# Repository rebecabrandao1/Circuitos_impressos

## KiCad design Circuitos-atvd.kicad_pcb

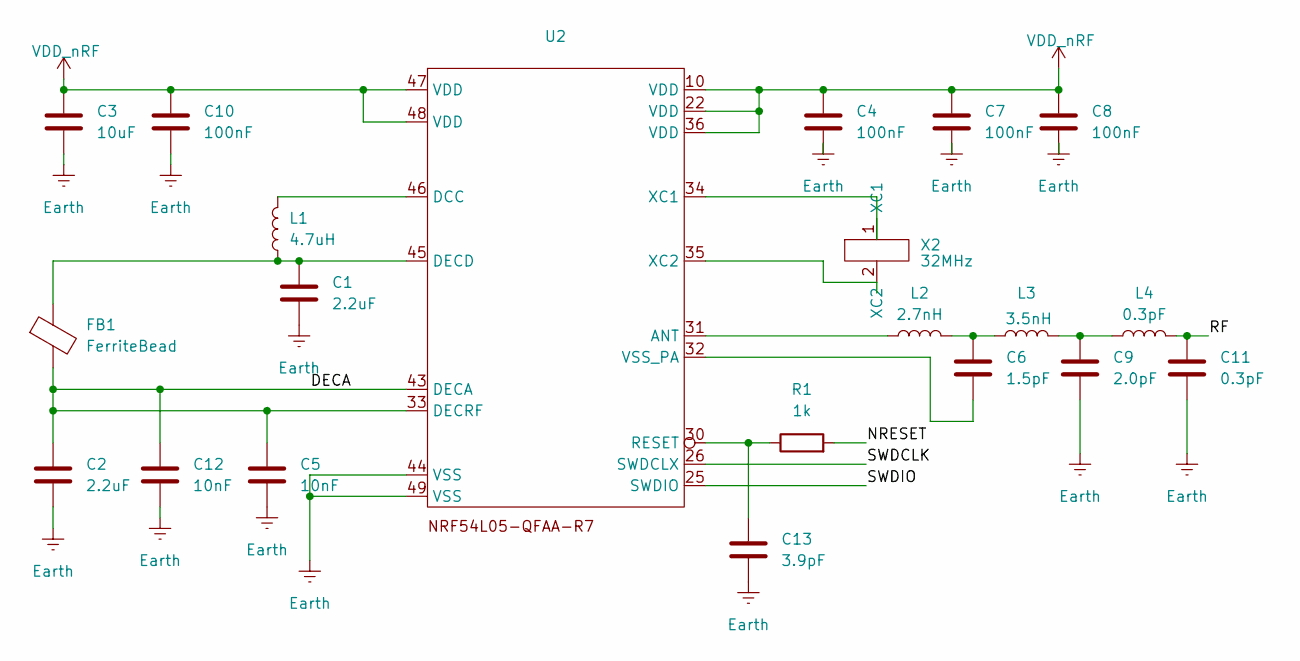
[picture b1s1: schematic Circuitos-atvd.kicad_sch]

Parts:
C1, C2: 2.2uF; C_0201_0603Metric
C3: 10uF; C_0402_1005Metric
C4, C7, C8, C10: 100nF; C_0201_0603Metric
C5, C12: 10nF; C_0201_0603Metric
C6: 1.5pF; C_0201_0603Metric
C9: 2.0pF; C_0201_0603Metric
C11: 0.3pF; C_0201_0603Metric
C13: 3.9pF; C_0201_0603Metric
FB1: FerriteBead; LairdTech_28C0236-0JW-10
L1: 4.7uH; L_0603_1608Metric
L2: 2.7nH; L_0201_0603Metric
L3: 3.5nH; L_0201_0603Metric
L4: 0.3pF; L_0201_0603Metric
R1: 1k; R_0201_0603Metric
U2: QFN-28-1EP_6x6mm_P0.65mm_EP4.25x4.25mm_ThermalVias
X2: 32MHz; Crystal_SMD_ECS_CSM3X-2Pin_7.6x4.1mm

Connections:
/DECA: C2.1, C5.1, C12.1, FB1.2, U2.33 (DECRF), U2.43 (DECA); also elsewhere on the board
/NRESET: R1.2
/RF: C11.1, L4.2
GND: C1.2, C2.2, C3.2, C4.2, C5.2, C7.2, C8.2, C9.2, C10.2, C11.2, C12.2, C13.2, U2.44 (VSS), U2.49 (VSS); also elsewhere on the board
unnamed: C6.1, L2.2, L3.1
unnamed: C9.1, L3.2, L4.1
unnamed 8: L2.1, U2.31 (ANT); also elsewhere on the board
unnamed 9: L1.2, U2.46 (DCC); also elsewhere on the board
unnamed 10: C1.1, FB1.1, L1.1, U2.45 (DECD); also elsewhere on the board
unnamed 11: C6.2, U2.32 (VSS_PA); also elsewhere on the board
unnamed 12: U2.34 (XC1), X2.1 (XC1); also elsewhere on the board
unnamed 13: C13.1, R1.1, U2.30 (RESET); also elsewhere on the board
VDD_nRF: C3.1, C4.1, C7.1, C8.1, C10.1, U2.10 (VDD), U2.22 (VDD), U2.36 (VDD), U2.47 (VDD), U2.48 (VDD); also elsewhere on the board

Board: 2 copper layers, 21 parts (0 on the bottom side), 12 nets, no tracks yet.

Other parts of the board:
U1: QFN-48-1EP_6x6mm_P0.4mm_EP4.2x4.2mm_ThermalVias

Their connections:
/DECA: U1.33 (DECRF), U1.43 (DECA); also elsewhere on the board
GND: U1.44 (VSS), U1.49 (VSS); also elsewhere on the board
unnamed 8: U1.31 (ANT); also elsewhere on the board
unnamed 9: U1.46 (DCC); also elsewhere on the board
unnamed 10: U1.45 (DECD); also elsewhere on the board
unnamed 11: U1.32 (VSS_PA); also elsewhere on the board
unnamed 12: U1.34 (XC1); also elsewhere on the board
unnamed 13: U1.30 (~RESET); also elsewhere on the board
VDD_nRF: U1.10 (VDD), U1.22 (VDD), U1.36 (VDD), U1.47 (VDD), U1.48 (VDD); also elsewhere on the board

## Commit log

2025-04-15 primeiro commit
2025-04-16 adicionando correcoes
